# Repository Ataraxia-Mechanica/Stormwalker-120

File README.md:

# Stormwalker 120

Discord server:

https://discord.gg/DXYpTaRm

Stormwalker 120 is a Voron 0 sized (120mm^3 build size), ultra fast 3D printer designed for rapid prototyping. Press and forget, go through iterations in minutes!

# Project Currently Under Construction

Progress is currently made towards an assembly manual covering how to build and tune this printer, though it's possible to build it from just the BOM and referencing the 3D model in Blender.

If sourcing the components are hard or expensive, please wait for the kit of this printer as I am determined to make it a reality.

# Input Shaper Graph

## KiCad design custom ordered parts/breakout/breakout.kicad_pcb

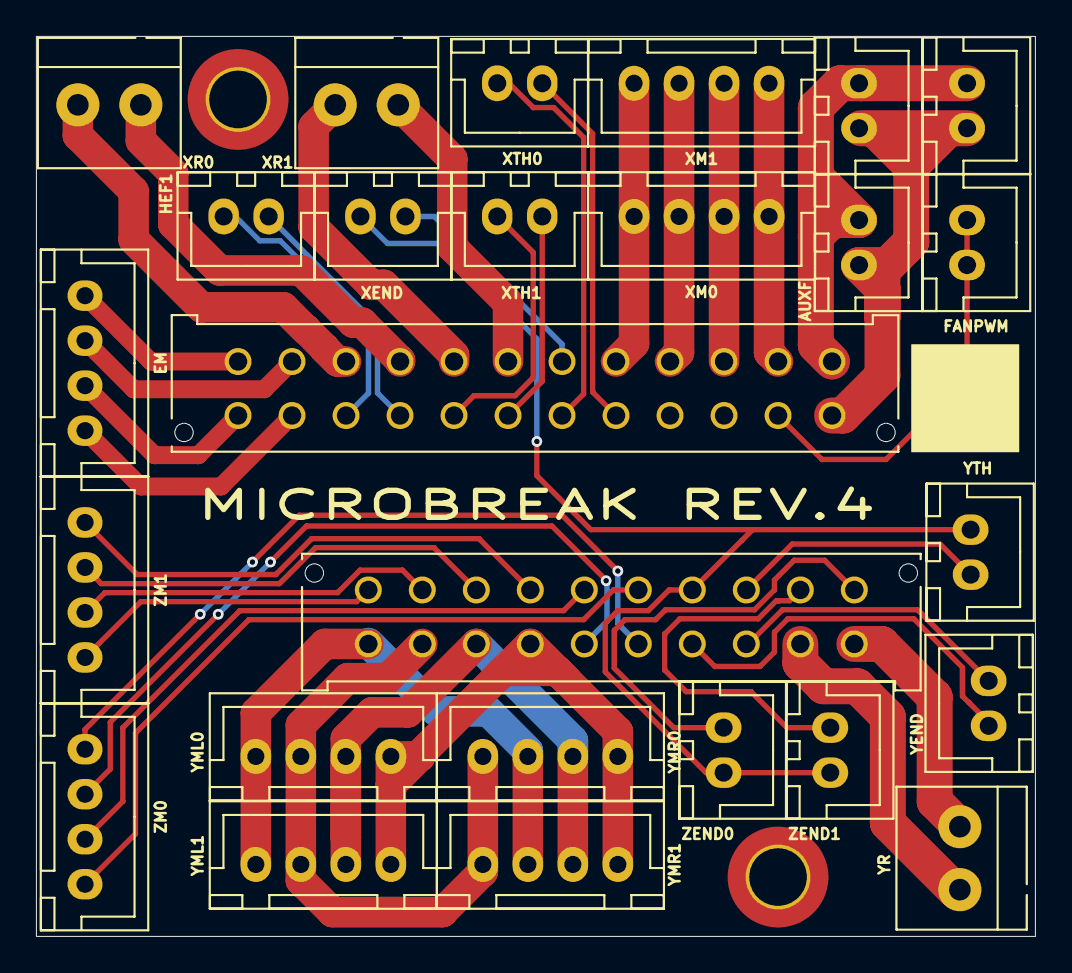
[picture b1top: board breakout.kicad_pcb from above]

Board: 2 copper layers, 55.5 x 50.0 mm, 28 parts (0 on the bottom side), 43 nets.

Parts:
AUXF, AUXF1, AUXF3: Fan; JST_XH_B2B-XH-A_1x02_P2.50mm_Vertical
EM: Conn_01x04_Socket; JST_XH_B4B-XH-A_1x04_P2.50mm_Vertical
FANPWM: Conn_01x02; JST_XH_B2B-XH-A_1x02_P2.50mm_Vertical
H1, H4: MountingHole_Pad; MountingHole_3.2mm_M3_DIN965_Pad_TopBottom
HEF1: Fan; JST_XH_B2B-XH-A_1x02_P2.50mm_Vertical
JX1: Conn_02x12_Top_Bottom; Molex_Micro-Fit_3.0_43045-2412_2x12_P3.00mm_Vertical
JY1: Conn_02x10_Top_Bottom; Molex_Micro-Fit_3.0_43045-2012_2x10_P3.00mm_Vertical
XEND: SW_Push; JST_XH_B2B-XH-A_1x02_P2.50mm_Vertical
XM0, XM1: Conn_01x04_Socket; JST_XH_B4B-XH-A_1x04_P2.50mm_Vertical
XR0, XR1: Heater; TerminalBlock_4Ucon_1x02_P3.50mm_Horizontal
XTH0, XTH1: Thermistor; JST_XH_B2B-XH-A_1x02_P2.50mm_Vertical
YEND: SW_Push; JST_XH_B2B-XH-A_1x02_P2.50mm_Vertical
YML0, YML1: Conn_01x04_Socket; JST_XH_B4B-XH-A_1x04_P2.50mm_Vertical
YMR0, YMR1: Conn_01x04_Socket; JST_XH_B4B-XH-A_1x04_P2.50mm_Vertical
YR: Heater; TerminalBlock_4Ucon_1x02_P3.50mm_Horizontal
YTH: Thermistor; JST_XH_B2B-XH-A_1x02_P2.50mm_Vertical
ZEND0, ZEND1: SW_Push; JST_XH_B2B-XH-A_1x02_P2.50mm_Vertical
ZM0, ZM1: Conn_01x04_Socket; JST_XH_B4B-XH-A_1x04_P2.50mm_Vertical

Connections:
GND: H1.1, H4.1, JX1.21, JX1.22
unnamed: AUXF.1 (+), AUXF1.1 (+), AUXF3.1 (+), JX1.24
unnamed: AUXF.2 (-), AUXF1.2 (-), AUXF3.2 (-), JX1.12
unnamed: EM.1, JX1.14
unnamed: EM.2, JX1.13
unnamed: EM.3, JX1.2
unnamed: EM.4, JX1.1
unnamed: FANPWM.1, FANPWM.2, JX1.23
unnamed: HEF1.1 (+), JX1.15
unnamed: HEF1.2 (-), JX1.16
unnamed: JX1.3, XR0.2
unnamed: JX1.4, XR0.1
unnamed: JX1.5, XR1.2
unnamed: JX1.6, XR1.1
unnamed: JX1.7, XEND.2
unnamed: JX1.8, XM0.1, XM1.1
unnamed: JX1.9, XM0.2, XM1.2
unnamed: JX1.10, XM0.3, XM1.3
unnamed: JX1.11, XM0.4, XM1.4
unnamed: JX1.17, XTH1.1
unnamed: JX1.18, XTH1.2
unnamed: JX1.19, XTH0.1
unnamed: JX1.20, XTH0.2
unnamed: JY1.1, YR.2
unnamed: JY1.2, YR.1
unnamed: JY1.3, YTH.1
unnamed: JY1.4, YTH.2
unnamed: JY1.5, ZM0.4
unnamed: JY1.6, ZM0.3
unnamed: JY1.7, YML0.1, YML1.1, YMR0.1, YMR1.1
unnamed: JY1.8, YML0.2, YML1.2, YMR0.2, YMR1.2
unnamed: JY1.9, YML0.3, YML1.3, YMR0.4, YMR1.4
unnamed: JY1.10, YML0.4, YML1.4, YMR0.3, YMR1.3
unnamed: JY1.11, ZEND0.2
unnamed: JY1.12, ZEND1.2
unnamed: JY1.13, YEND.1
unnamed: JY1.14, XEND.1, YEND.2, ZEND0.1, ZEND1.1
unnamed: JY1.15, ZM0.1
unnamed: JY1.16, ZM0.2
unnamed: JY1.17, ZM1.4
unnamed: JY1.18, ZM1.3
unnamed: JY1.19, ZM1.2
unnamed: JY1.20, ZM1.1

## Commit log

2025-09-26 Stormwalker 1.0 prerelease
2025-09-26 Reinforce extruder idler
    Broke again :(
2025-09-29 Oops, forgot the nozzle
2025-09-29 Ignore more kicad temp files
2025-09-29 Use SMT thermistor on the bed which is more reliable and cheaper
2025-09-29 Dish soap
2025-09-29 Bed wiring update
    Strain Relief and bigger holes on the breakout pcb cover
2025-09-29 Fix Z column geometry
2025-09-30 Add IS graph
2025-09-30 Forgot 4 Screws, literally unbuildable
2025-10-05 Add dust cover for X axis extrusion
2025-10-11 Strengthened the extruder further
    Now handles filled filaments in a heated chamber well
2025-10-15 Switch to PET for some parts for heat resistance
2025-10-15 Tilt the grub screw access hole to the right
2025-10-22 Fix small error in strain relief
2025-10-22 Polymide bed heater
2025-11-02 Complete overhaul
    Many changes are made, using more efficient/rigid components.
2025-11-02 Add discord server
